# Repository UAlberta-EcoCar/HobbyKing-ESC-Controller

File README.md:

# ESC Controller for Hobby King ESC

## To do list:
* ~~ESC Controller~~
	```
	Pinout for ESC:
		* Orange - Signal
		* Red - 5V
		* Brown - GND
	```
* ~~CAN Bus~~
* Pedal
* Brakes
* ~~Encoder~~
* Current Sensing
* FTDI (chip/headers)
* Status LEDS

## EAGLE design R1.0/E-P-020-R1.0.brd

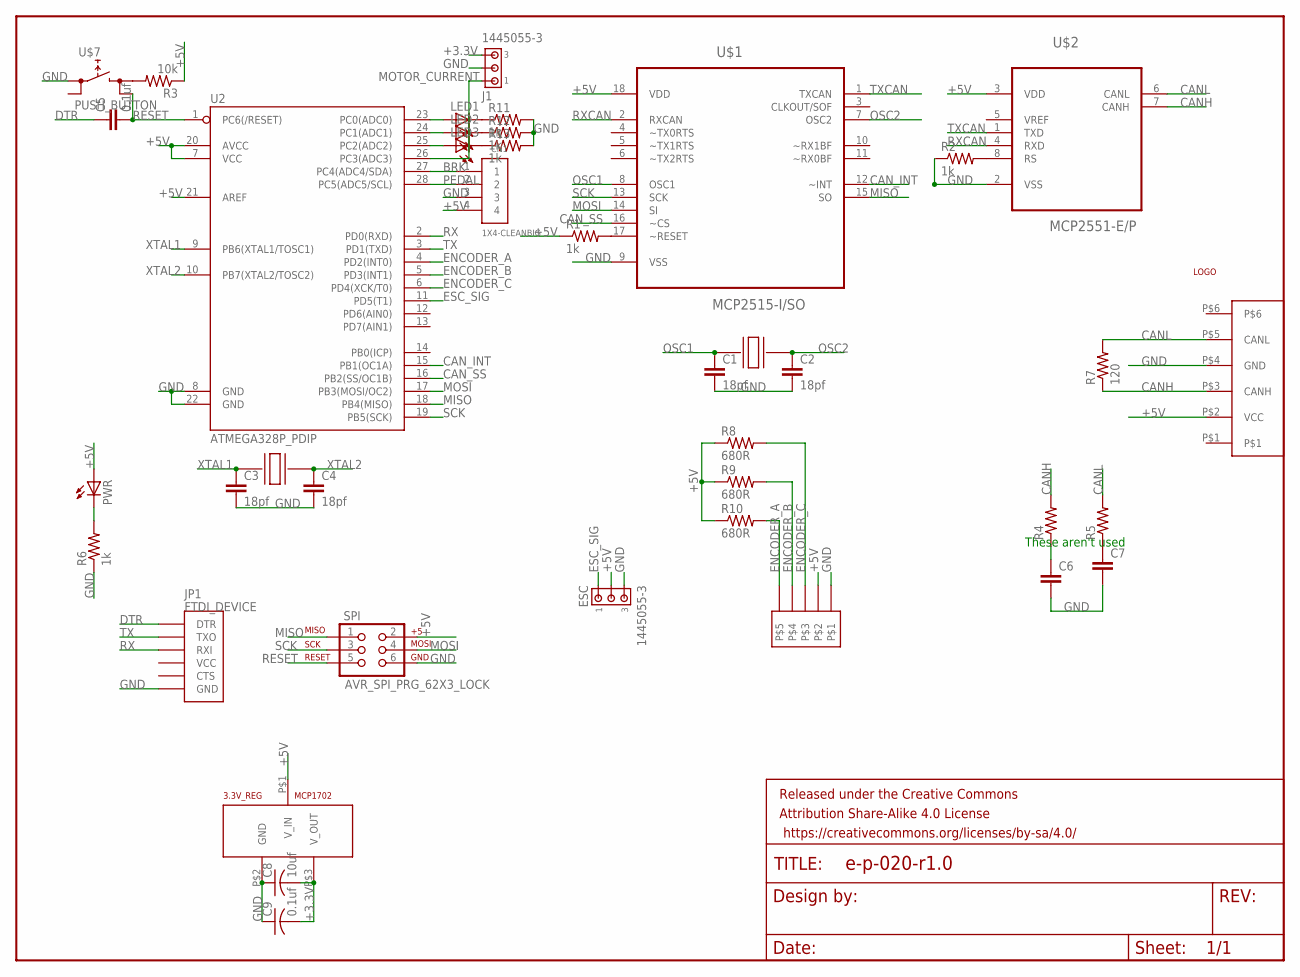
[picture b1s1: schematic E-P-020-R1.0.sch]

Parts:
3.3V_REG: MCP1702; SOT-23A
C1, C2, C3, C4: 18pf; 0805
C5: 0.1uf; 0805
C6, C7: CAP0805; 0805
C8: 10uf; C0805
C9: 0.1uf; C0805
CAN-BUS: CAN_6P6C
CN1: 1X4-CLEANBIG; 1X04-CLEANBIG
ENCODER: 5_PIN_MICRO_MATE_N_LOCK
ESC: 1445055-3
FRAME1: FRAME-LETTERNO_PACKAGE; DUMMY
J1: 1445055-3
JP1: FTDI_DEVICE; FTDI_DEVICE_SIDE
LED1, LED2, LED3: LEDSMT1206; 1206
PWR: LEDCHIPLED_1206; CHIPLED_1206
R1, R2, R6, R11, R12, R13: 1k; 0805
R3: 10k; 0805
R4, R5: RESISTOR0805-RES; 0805
R7: 120; M1206
R8, R9, R10: 680R; 0805
SPI: AVR_SPI_PRG_62X3_LOCK; 2X3_LOCK
U2: ATMEGA328P_PDIP; DIL28-3
U$1: MCP2515-I/SO; SOIC127P1034X264-18N
U$2: MCP2551-E/P; DIP254P762X432-8
U$3, U$4: CRYSTAL; 7A_CRYSTAL
U$6: LOGO
U$7: PUSH_BUTTON; PUSHBUTTON

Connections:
+3.3V: 3.3V_REG.P$3 (V_OUT), C8.2, C9.2, J1.3
+5V: 3.3V_REG.P$1 (V_IN), CAN-BUS.P$2 (VCC), CN1.4, ENCODER.P$4, ESC.2, PWR.A, R1.1, R3.1, R8.1, R9.1, R10.1, SPI.2, U2.7 (VCC), U2.20 (AVCC), U2.21 (AREF), U$1.18 (VDD), U$2.3 (VDD)
BRK: CN1.1, U2.27 (PC4(ADC4/SDA))
CANH: CAN-BUS.P$3 (CANH), R4.2, R7.1, U$2.7 (CANH)
CANL: CAN-BUS.P$5 (CANL), R5.2, R7.2, U$2.6 (CANL)
CAN_INT: U2.15 (PB1(OC1A)), U$1.12 (~INT)
CAN_SS: U2.16 (PB2(SS/OC1B)), U$1.16 (~CS)
DTR: C5.1, JP1.P$1 (DTR)
ENCODER_A: ENCODER.P$1, R10.2, U2.4 (PD2(INT0))
ENCODER_B: ENCODER.P$2, R9.2, U2.5 (PD3(INT1))
ENCODER_C: ENCODER.P$3, R8.2, U2.6 (PD4(XCK/T0))
ESC_SIG: ESC.1, U2.11 (PD5(T1))
GND: 3.3V_REG.P$2 (GND), C1.2, C2.2, C3.2, C4.2, C6.2, C7.2, C8.1, C9.1, CAN-BUS.P$4 (GND), CN1.3, ENCODER.P$5, ESC.3, J1.2, JP1.P$6 (GND), R2.1, R6.1, R11.2, R12.2, R13.2, SPI.6, U2.8 (GND), U2.22 (GND), U$1.9 (VSS), U$2.2 (VSS), U$7.L1 (L)
MISO: SPI.1, U2.18 (PB4(MISO)), U$1.15 (SO)
MOSI: SPI.4, U2.17 (PB3(MOSI/OC2)), U$1.14 (SI)
MOTOR_CURRENT: J1.1, U2.26 (PC3(ADC3))
unnamed: R1.2, U$1.17 (~RESET)
unnamed: R2.2, U$2.8 (RS)
unnamed: C6.1, R4.1
unnamed: R3.2, U$7.R1 (R)
unnamed: C7.1, R5.1
unnamed: LED1.A, U2.23 (PC0(ADC0))
unnamed: LED2.A, U2.24 (PC1(ADC1))
unnamed: PWR.C, R6.2
unnamed: LED3.A, U2.25 (PC2(ADC2))
unnamed: LED1.C, R11.1
unnamed: LED2.C, R12.1
unnamed: LED3.C, R13.1
OSC1: C1.1, U$1.8 (OSC1), U$3.P$2
OSC2: C2.1, U$1.7 (OSC2), U$3.P$1
PEDAL: CN1.2, U2.28 (PC5(ADC5/SCL))
RESET: C5.2, SPI.5, U2.1 (PC6(/RESET)), U$7.R2 (R)
RX: JP1.P$3 (RXI), U2.2 (PD0(RXD))
RXCAN: U$1.2 (RXCAN), U$2.4 (RXD)
SCK: SPI.3, U2.19 (PB5(SCK)), U$1.13 (SCK)
TX: JP1.P$2 (TXO), U2.3 (PD1(TXD))
TXCAN: U$1.1 (TXCAN), U$2.1 (TXD)
XTAL1: C3.1, U2.9 (PB6(XTAL1/TOSC1)), U$4.P$2
XTAL2: C4.1, U2.10 (PB7(XTAL2/TOSC2)), U$4.P$1

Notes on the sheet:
These aren't used

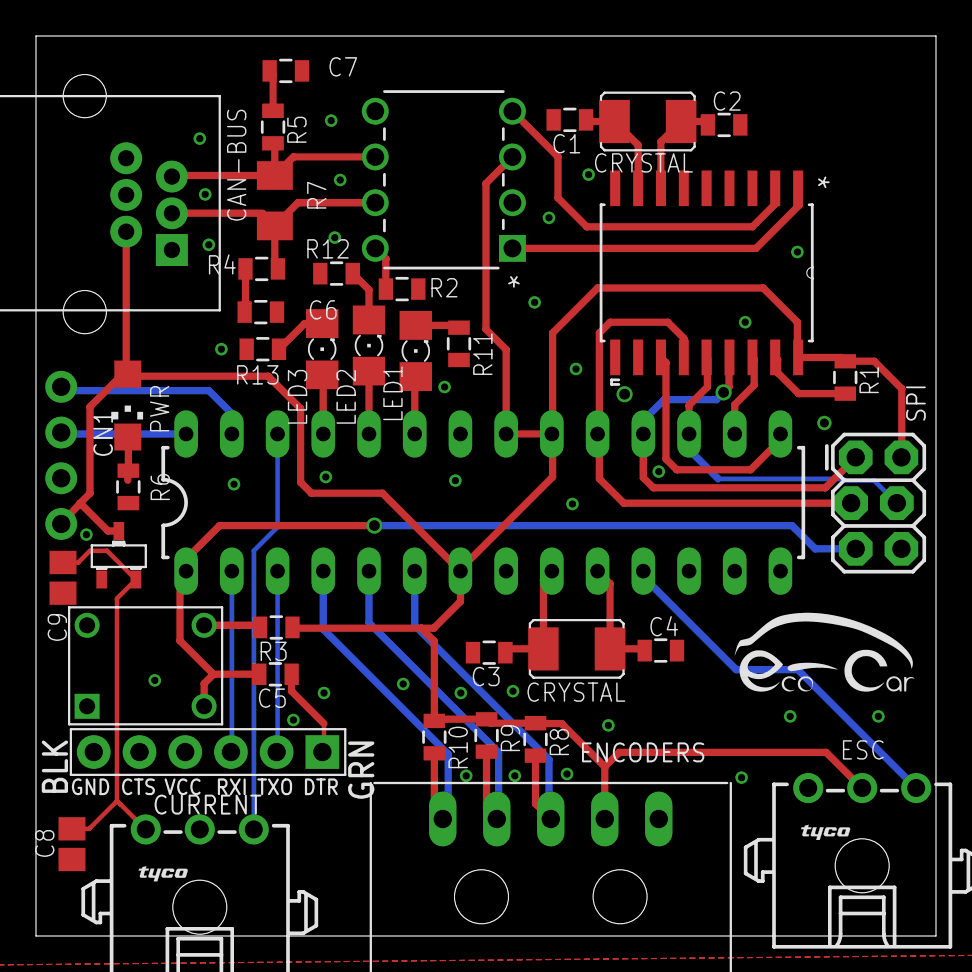
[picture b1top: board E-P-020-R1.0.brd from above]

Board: 2 copper layers, 50.0 x 50.0 mm, 42 parts (0 on the bottom side), 39 nets.

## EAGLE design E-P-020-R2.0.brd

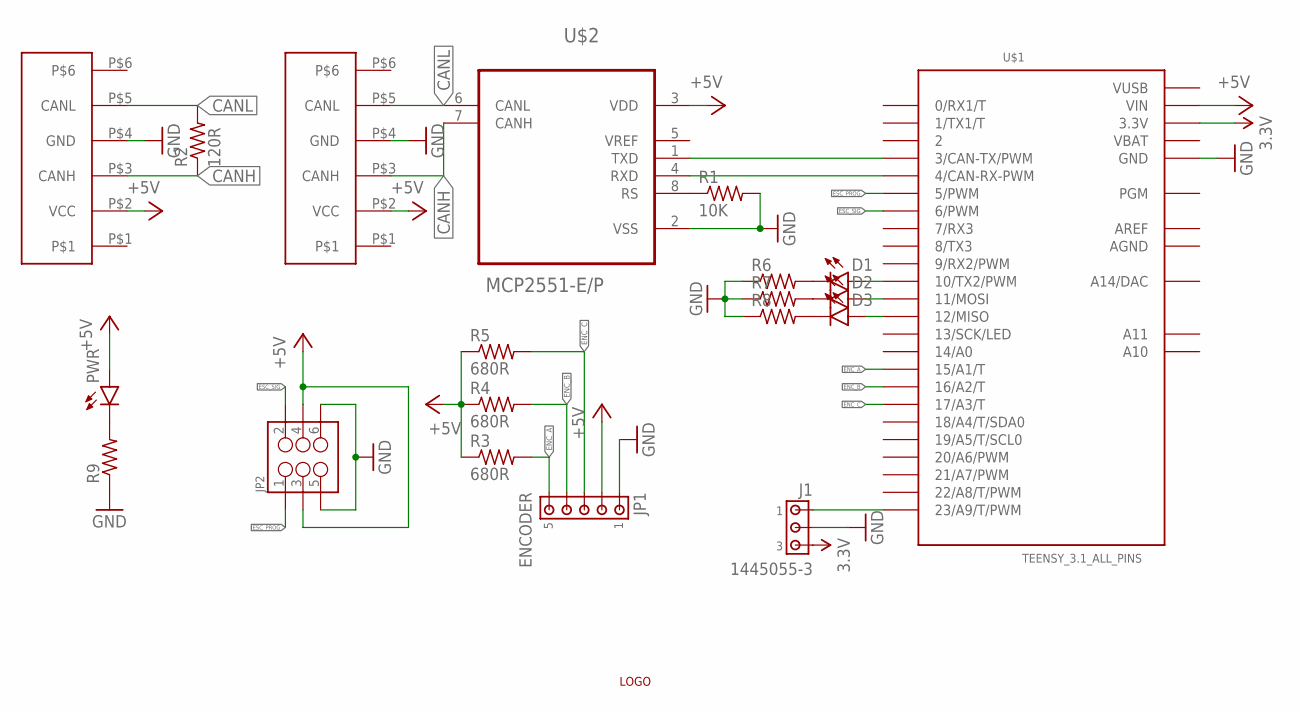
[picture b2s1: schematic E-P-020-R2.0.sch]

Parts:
D1, D2, D3: BLUE; LED-1206
J1: 1445055-3
JP1: ENCODER; 1445055-5
JP2: M03X2POGO_PINS; 2X3_POGO
PWR: BLUE; LED-1206
R1: 10K; R0805
R2: 120R; M1206
R3, R4, R5: 680R; M0805
R6, R7, R8, R9: R-US_M1206; M1206
U$1: TEENSY_3.1_ALL_PINS; TEENSY3-ALL_PINS
U$2: MCP2551-E/P; DIP254P762X432-8
U$3, U$5: CAN_6P6C
U$4: LOGO

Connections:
3.3V: J1.3, U$1.3.3V, U$1.3.3V1 (3.3V)
+5V: JP1.2, JP2.P$3 (3), JP2.P$4 (4), PWR.A, R3.1, R4.1, R5.1, U$1.VIN, U$2.3 (VDD), U$3.P$2 (VCC), U$5.P$2 (VCC)
AGND: U$1.AGND
AREF: U$1.AREF
CANH: R2.1, U$2.7 (CANH), U$3.P$3 (CANH), U$5.P$3 (CANH)
CANL: R2.2, U$2.6 (CANL), U$3.P$5 (CANL), U$5.P$5 (CANL)
ENC_A: JP1.5, R3.2, U$1.15/A1 (15/A1/T)
ENC_B: JP1.4, R4.2, U$1.16/A2 (16/A2/T)
ENC_C: JP1.3, R5.2, U$1.17/A3 (17/A3/T)
ESC_PROG: JP2.P$1 (1), U$1.5 (5/PWM)
ESC_SIG: JP2.P$2 (2), U$1.6 (6/PWM)
GND: J1.2, JP1.1, JP2.P$5 (5), JP2.P$6 (6), R1.2, R6.1, R7.1, R8.1, R9.1, U$1.GND, U$1.GND1 (GND), U$2.2 (VSS), U$3.P$4 (GND), U$5.P$4 (GND)
unnamed: U$1.4 (4/CAN-RX-PWM), U$2.4 (RXD)
unnamed: U$1.3 (3/CAN-TX/PWM), U$2.1 (TXD)
unnamed: R1.1, U$2.8 (RS)
unnamed: J1.1, U$1.23/A9 (23/A9/T/PWM)
unnamed: D3.C, R8.2
unnamed: D2.C, R7.2
unnamed: D1.C, R6.2
unnamed: D3.A, U$1.12 (12/MISO)
unnamed: D2.A, U$1.11 (11/MOSI)
unnamed: D1.A, U$1.10 (10/TX2/PWM)
unnamed: PWR.C, R9.2
VBAT: U$1.VBAT
VUSB: U$1.VUSB

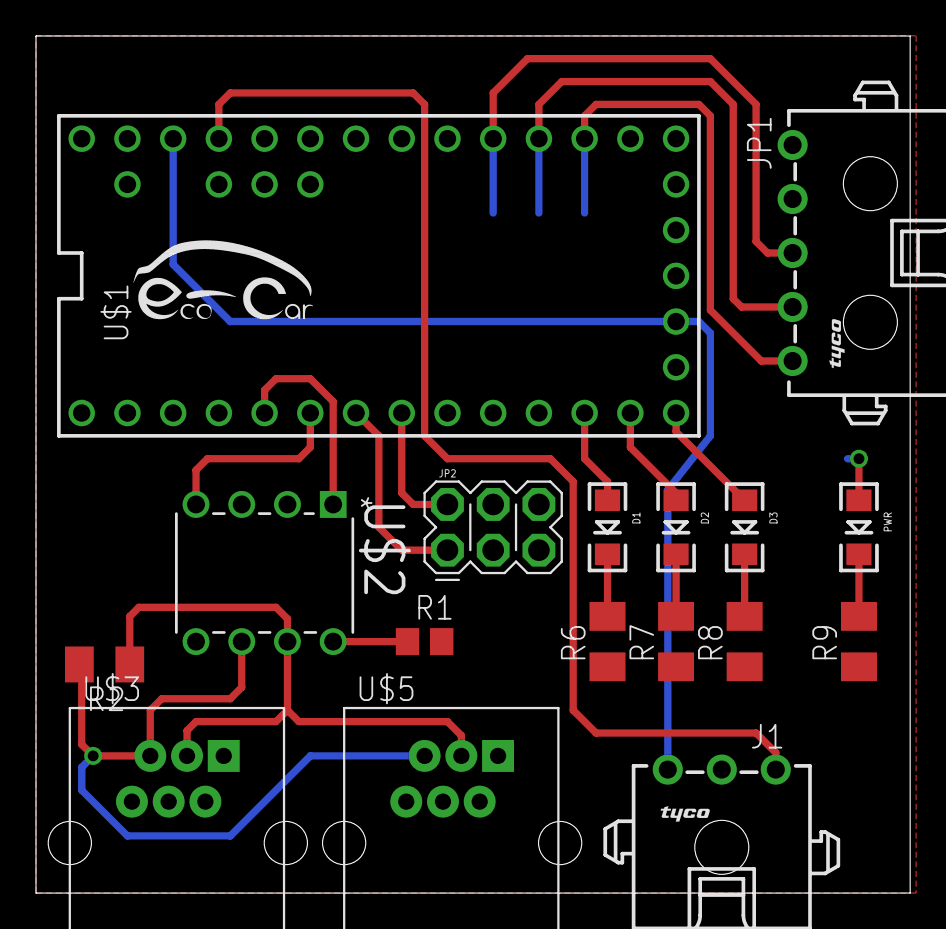
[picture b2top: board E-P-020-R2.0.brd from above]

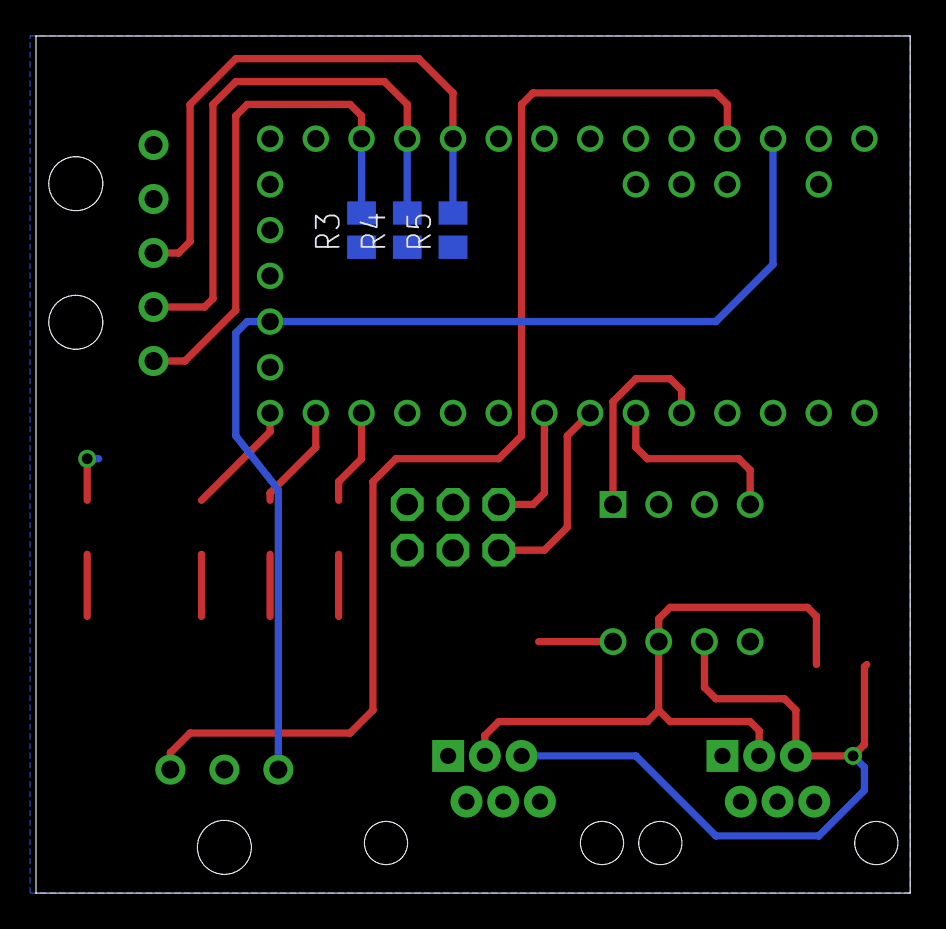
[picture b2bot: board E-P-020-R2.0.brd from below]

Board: 2 copper layers, 48.6 x 47.6 mm, 21 parts (3 on the bottom side), 21 nets.

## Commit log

2016-02-14 updated readme with todo list
2016-02-14 Added ESC and Encoder
2016-02-14 Should be good to go
2016-02-15 Complete
2016-02-17 Created esc controller with teensy
2016-02-17 Added version number to board
2016-03-03 Added resistor/capacitor values
2016-03-14 Integrated pedal, started working on the current sensor
2016-03-16 Motor running over can bus
2016-03-17 Speed code with functiions. To be implemented over CAN
2016-03-19 moved files to MC_Firmware
2016-06-05 SEMA 2016 changes

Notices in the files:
parts and their libraries:
SparkFun-DigitalIC: Licensing: Creative Commons ShareAlike 4.0 International - https://creativecommons.org/licenses/by-sa/4.0
SparkFun-Aesthetics: Released under the Creative Commons Attribution Share-Alike 4.0 License
SparkFun-Aesthetics: https://creativecommons.org/licenses/by-sa/4.0
